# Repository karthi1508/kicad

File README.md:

# kicad
This repository contains my KiCad projects, including PCB layouts, schematics, and electronic hardware designs created as part of my learning and engineering projects.

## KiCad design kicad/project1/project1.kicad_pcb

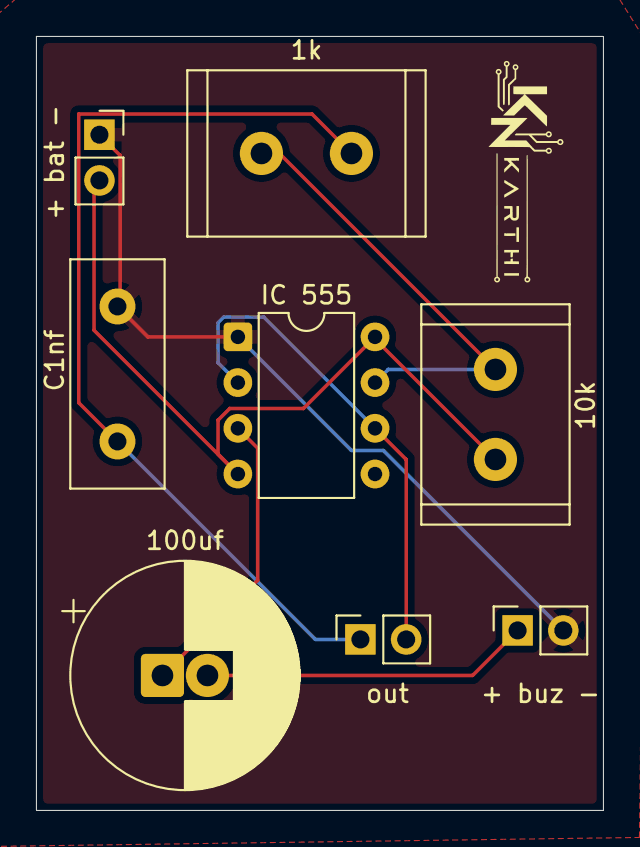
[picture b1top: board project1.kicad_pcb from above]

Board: 2 copper layers, 31.5 x 43.0 mm, 8 parts (0 on the bottom side), 7 nets.

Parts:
1k: 10k; R_Radial_Power_L13.0mm_W9.0mm_P5.00mm
10k: 1k; R_Radial_Power_L12.0mm_W8.0mm_P5.00mm
100uf: C_Polarized; CP_Radial_D12.5mm_P2.50mm
+ bat -: battery; PinSocket_1x02_P2.54mm_Vertical
+ buz -: buzzer; PinSocket_1x02_P2.54mm_Vertical
C1nf: C; C_Disc_D12.5mm_W5.0mm_P7.50mm
IC 555: NE555P; DIP-8_W7.62mm
out: hoomans; PinSocket_1x02_P2.54mm_Vertical

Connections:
GND: + bat -.1, + buz -.2, C1nf.1, IC 555.1 (GND)
unnamed: 1k.2, C1nf.2, out.1
unnamed: 100uf.2, + buz -.1
unnamed: 1k.1, 10k.2, IC 555.7 (DISCH)
unnamed: 100uf.1, IC 555.3 (OUT)
unnamed: IC 555.2 (TRIG), IC 555.6 (THRES), out.2
VCC: 10k.1, + bat -.2, IC 555.4 (~RST), IC 555.8 (VCC)
